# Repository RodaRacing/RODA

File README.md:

# Car Hotspot Automation (Kotlin)

Implementación base para automatizar el encendido/apagado del hotspot en función de la conexión Bluetooth del coche.

## Entregables incluidos

- `CarBluetoothReceiver.kt`: escucha `BluetoothDevice.ACTION_ACL_CONNECTED` y `ACTION_ACL_DISCONNECTED`, filtra por MAC/nombre y notifica al servicio.
- `HotspotForegroundService.kt`: mantiene proceso en primer plano con notificación persistente e intenta gestionar hotspot según versión de Android.
- `AndroidManifest.xml`: permisos, receiver y foreground service.

## Consideraciones Android 11/12/13+

1. **No existe API pública estable para activar/desactivar tethering completo** (compartir datos móviles) para apps de terceros.
2. `TetheringManager.startTethering(...)` normalmente requiere permisos privilegiados (`TETHER_PRIVILEGED`), reservados para apps de sistema/OEM.
3. `WRITE_SETTINGS` puede servir en escenarios legacy, pero en Android modernos ya no garantiza el control total del hotspot.
4. La alternativa soportada por API pública es `WifiManager.startLocalOnlyHotspot()`, que **no comparte internet móvil**.
5. En práctica, para Android 11+ la estrategia recomendada para apps normales es:
   - Abrir la pantalla de ajustes de hotspot mediante `Intent` (ej. `Settings.ACTION_WIRELESS_SETTINGS` o pantalla específica del OEM).
   - Opcionalmente usar automatización por accesibilidad (con consentimiento explícito del usuario), sabiendo que es más frágil por cambios de UI.

## Permisos clave

- `BLUETOOTH_CONNECT` (Android 12+)
- `ACCESS_FINE_LOCATION` (compatibilidad de metadatos/escaneo BT en versiones previas)
- `FOREGROUND_SERVICE`
- `WRITE_SETTINGS` (permiso especial: el usuario debe habilitarlo manualmente en ajustes)

## Nota práctica

Si necesitas una solución robusta sin pelear con restricciones OEM/API, considera herramientas como **MacroDroid** o **Tasker**, que ya cubren parte de estos flujos de automatización con configuraciones del usuario.

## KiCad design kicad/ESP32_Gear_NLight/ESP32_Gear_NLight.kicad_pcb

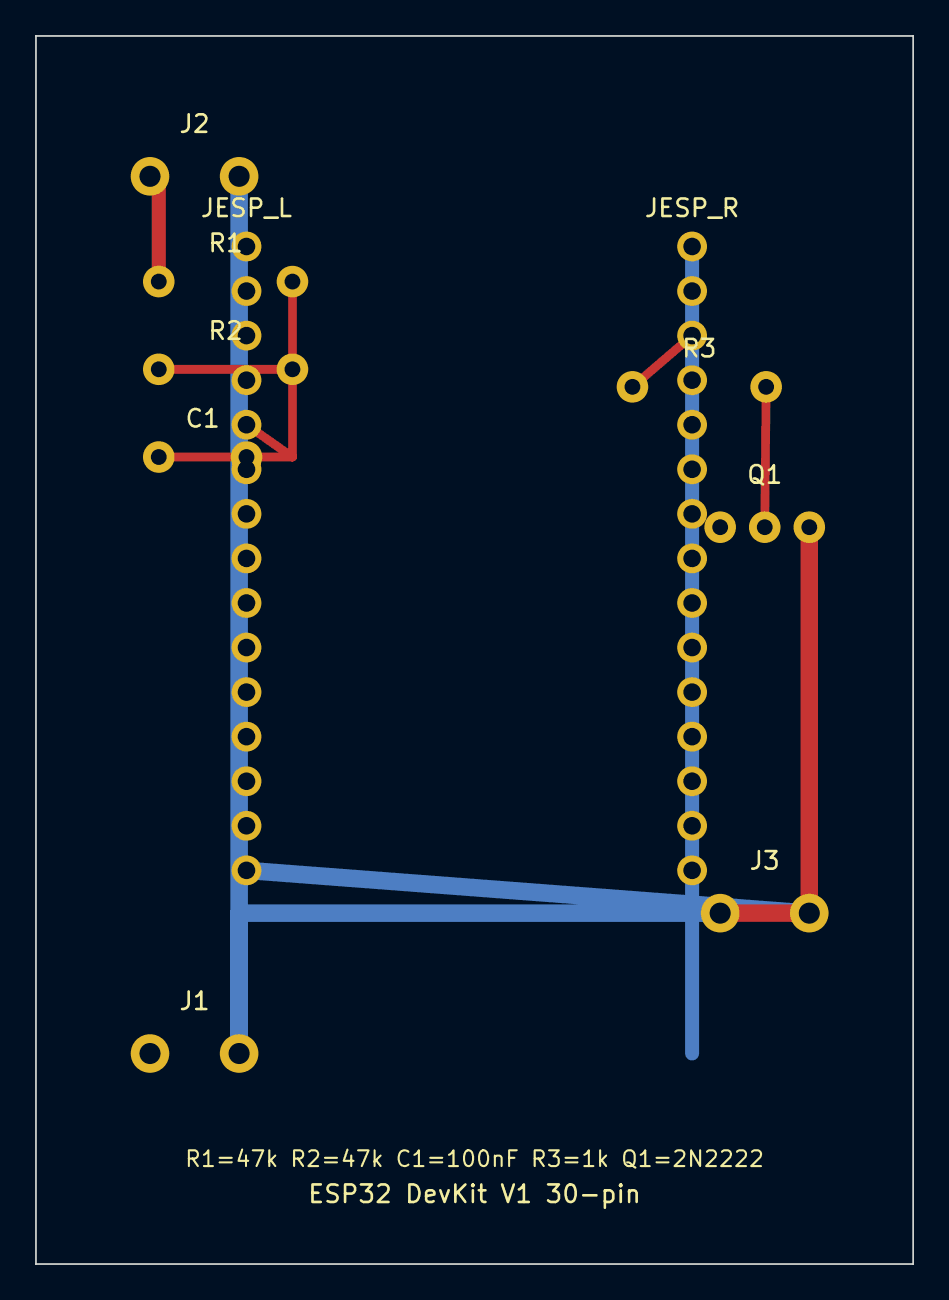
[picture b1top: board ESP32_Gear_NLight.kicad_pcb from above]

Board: 2 copper layers, 50.0 x 70.0 mm, 10 parts (0 on the bottom side), 6 nets.

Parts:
C1: 100nF; C1_100N
J1: 12V_IN_GND; J1_12V_2P_5.08
J2: SENSOR_GND; J2_SENSOR_2P_5.08
J3: N_LIGHT_GND; J3_NLIGHT_2P_5.08
JESP_L: ESP32_LEFT; JESP_L_1x15_2.54
JESP_R: ESP32_RIGHT; JESP_R_1x15_2.54
Q1: 2N2222; Q1_2N2222_TO92
R1: 47k; R1_47K
R2: 47k; R2_47K
R3: 1k; R3_1K

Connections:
ADC_IN: C1.1, JESP_L.5, R1.2, R2.1
BASE: Q1.2, R3.2
GND: C1.2, J1.2, J2.2, J3.2, JESP_L.15, JESP_R.2, Q1.1, R2.2
GPIO_D23: JESP_R.3, R3.1
N_LIGHT: J3.1, Q1.3
SENSOR_IN: J2.1, R1.1

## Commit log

2025-07-01 Add simple quiz app for FP automotive studies
2025-07-01 Add README instructions
2026-02-25 Add KiCad project for ESP32 gear sensor PCB
2026-03-01 Mejorar copy detallado y layout premium orientado a motos
2026-03-01 Añadir chat IA ITV para evaluar reformas de accesorios
2026-03-01 Hacer funcional el chat ITV con carga y consulta real de PDFs
2026-03-01 Persistir PDFs en base compartida para consultas ITV
2026-03-02 Ocultar botón de subida de PDFs para usuarios finales
2026-03-02 Habilitar acceso admin desde UI para subir PDFs
2026-03-02 Añadir segmento trail/touring premium con packs recomendados
2026-03-02 Add Bluetooth-driven hotspot foreground service scaffold
